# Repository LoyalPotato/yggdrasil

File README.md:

<div align="center">
  
</div>

</br>
</br>

# Welcome

[![CC BY-NC-SA 4.0][cc-by-nc-sa-shield]][cc-by-nc-sa]

This is the home of my first keyboard project that I dubbed `Yggdrasil`.

It's a 36% split keyboard that is tailored to be comfortable to my hand span. You can find the build guide [here](./docs/build.md).

You can view [here](https://www.youtube.com/watch?v=r2uFzhUAN9s) to see it in action.

Here's what it looks like (minus plates)

And with 3d printed plates (and custom cables also done by me hehe :) )

Full wrap around case, also 3d printed

## Contents

- [Welcome](#welcome)
  - [Contents](#contents)
  - [Design Article](#design-article)
  - [Plans](#plans)
  - [References](#references)
  - [License](#license)

## Design Article

If you're interested in knowing more about the design process that I went through and the final cost for me (in Portugal), I wrote a [post](https://loyalpotato.com/projects/yggdrasil) about it :)

## Plans

You can go to the projects tab to see what my current plans for the first version of this board are.

~~I do plan on making a low profile kailh choc variant, but only after I complete the cherry variant will I start working on a choc one.~~ I ended up using a footprint that has support for both :)

At some point I also would like to add to each version an alternative with a rotary encoder, and will create separate variants for that as well.

After I get more familiar with the process of pcb design and manufacturing I'd like to have a try at having a modular pcb, like the corne, where we can break the extra keys that you don't need.

---

## References

- [Ergogen](https://github.com/ergogen/ergogen) and the kind people from their [discord](https://discord.gg/nbKcAZB)
- [Ben Vallack's](https://github.com/benvallack/ergogen) flipper ergogen config and his youtube [video](https://www.youtube.com/watch?v=UKfeJrRIcxw)
- [Corne Kbd](https://github.com/foostan/crkbd)
- [ruiqimao's guide](https://github.com/ruiqimao/keyboard-pcb-guide)
- [tapioki's Architeuthis dux](https://github.com/tapioki/cephalopoda/tree/main/Architeuthis%20dux)
- [Lily58](https://github.com/kata0510/Lily58)
- [Keyboard Atelier's Discord](https://discord.gg/b7vwhHS)

## License

This work is licensed under a [Creative Commons Attribution-ShareAlike 4.0 International License][cc-by-nc-sa].

[![CC BY-NC-SA 4.0][cc-by-nc-sa-image]][cc-by-nc-sa]

[cc-by-nc-sa]: http://creativecommons.org/licenses/by-nc-sa/4.0/
[cc-by-nc-sa-image]: https://licensebuttons.net/l/by-nc-sa/4.0/88x31.png
[cc-by-nc-sa-shield]: https://img.shields.io/badge/License-CC%20BY--NC--SA%204.0-lightgrey.svg

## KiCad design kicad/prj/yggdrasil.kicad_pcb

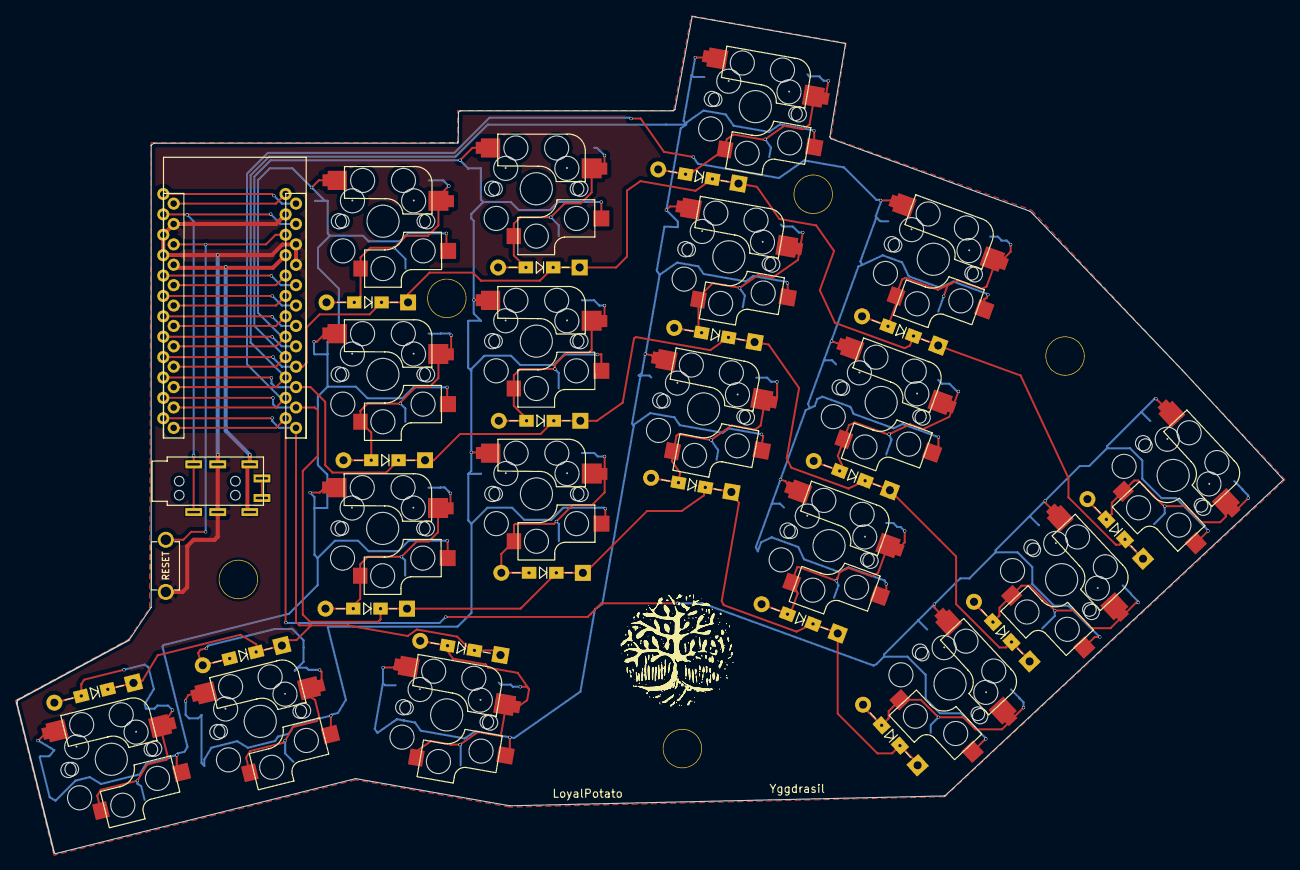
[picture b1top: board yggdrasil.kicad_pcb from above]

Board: 2 copper layers, 157.8 x 104.3 mm, 44 parts (0 on the bottom side), 31 nets.

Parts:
D1, D2, D3, D4, D5, D6, D7, D8, D9, D10, D11, D12, D13, D14, D15, D16, D17, D18: D; Diode_TH_SOD123
J2: 4PIN; MJ-4PP-9
RSW1: SW_RST; TACT_SWITCH_TVBP06
SW1, SW2, SW3, SW4, SW5, SW6, SW7, SW8, SW9, SW10, SW11, SW12, SW13, SW14, SW15, SW16, SW17, SW18: SW_PUSH; Cherry_MX_Choc_Hotswap_MX_Spacing
TH3, TH4, TH5, TH6, TH7: HOLE; HOLE_M2_TH
U1: ProMicro; ProMicro_USB_C

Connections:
DATA: J2.3, U1.2 (RX(PD2))
GND: J2.2, RSW1.1, U1.3 (GND), U1.4 (GND), U1.23 (GND)
unnamed: D1.2 (A), SW1.2
unnamed: D2.2 (A), SW2.2
unnamed: D3.2 (A), SW3.2
unnamed: D4.2 (A), SW4.2
unnamed: D5.2 (A), SW5.2
unnamed: D6.2 (A), SW6.2
unnamed: D7.2 (A), SW7.2
unnamed: D8.2 (A), SW8.2
unnamed: D9.2 (A), SW9.2
unnamed: D10.2 (A), SW10.2
unnamed: D11.2 (A), SW11.2
unnamed: D12.2 (A), SW12.2
unnamed: D13.2 (A), SW13.2
unnamed: D14.2 (A), SW14.2
unnamed: D15.2 (A), SW15.2
unnamed: D16.2 (A), SW16.2
unnamed: D17.2 (A), SW17.2
unnamed: D18.2 (A), SW18.2
RESET: RSW1.2, U1.22 (RST)
VCC: J2.1, U1.21 (VCC)
col0: SW1.1, SW6.1, SW11.1, SW16.1, U1.17 (A0(PF7))
col1: SW2.1, SW7.1, SW12.1, SW17.1, U1.16 (D15(PB1))
col2: SW3.1, SW8.1, SW13.1, SW18.1, U1.15 (D14(PB3))
col3: SW4.1, SW9.1, SW14.1, U1.14 (D16(PB2))
col4: SW5.1, SW10.1, SW15.1, U1.13 (D10(PB6))
row0: D1.1 (K), D2.1 (K), D3.1 (K), D4.1 (K), D5.1 (K), U1.9 (D6(PD7))
row1: D6.1 (K), D7.1 (K), D8.1 (K), D9.1 (K), D10.1 (K), U1.10 (D7(PE6))
row2: D11.1 (K), D12.1 (K), D13.1 (K), D14.1 (K), D15.1 (K), U1.11 (D8(PB4))
row3: D16.1 (K), D17.1 (K), D18.1 (K), U1.12 (D9(PB5))

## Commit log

2022-02-21 Capitalize
2022-02-21 Add build doc for cherry variant
2022-02-21 Doc file for choc switches build guide
2022-02-21 Renaming and re-structuring
2022-02-21 Add logos
2022-02-21 Test logos in readme
2022-02-21 Remove no bg logo and reduce size
2022-02-21 Add logo with name
2022-02-21 Use named version for logo
2022-02-21 Update readme with refs, content and plans
2022-02-21 Add ergogen file configurations and notes
2022-02-21 Update plans
2022-02-21 Remove one spacing
2022-02-21 Add outlines for keycaps and edge from ergogen config
2022-02-21 Re organize ergogen folder
2022-02-21 Add description to ergogen config sections
2022-02-23 Update logo with text
2022-02-23 Remove variants and replace with single version that will support both types
2022-02-23 Add kicad backup folder to gitignore
2022-02-24 Outlines v1
2022-02-28 Lily58 footprints
2022-02-28 kbd footprints
2022-02-28 kbd symbol lib
2022-02-28 Lily58 symbol lib
2022-02-28 Kicad project
2022-03-01 Add custom footprints Hotswap switch with cherry keycap spacing Different measurements for promicro with usb-c
2022-03-01 Updated spacing Re-do edge cuts Some routing Diode placement Screwhole placement
2022-03-02 Logo with and without text in png format for kicad
2022-03-02 Change switch keycap spacing Add routing Add ground plane Add logo & text
2022-03-02 Footprint for logo
2022-03-02 Files missed in previous commits
2022-03-03 Update readme plans and refs
2022-03-03 Clean up/straighten routings
2022-03-03 Add image with board outline and switch placement
2022-03-03 Kicad prj update
2022-03-03 Change license
2022-03-03 Update with license
2022-03-03 Re update license section
2022-03-03 Re-update license
2022-03-03 Update license title
2022-03-03 Update license link ref
2022-03-03 Add gerber
2022-03-03 Prj files
2022-03-05 Add plates for first revision Still need to confirm if everything works out
2022-03-05 Deleted outlines folder as I haven't used it so far
2022-03-05 Revision 1.0.1 Fixed wrong rotation, some spacing and clearences
2022-03-05 Rev 1 prj
2022-03-05 Some revision notes
2022-03-05 Remove backup folders
2022-03-05 Add small description of the keyboard
2022-03-05 Update build with part list that I will be using
2022-03-05 Change TRRS jack ( ordered smd ;w;)
2022-04-04 Fix USB-C ProMicro link
2022-04-30 Build guide almost finished
2022-04-30 Add semi final image to cover
2022-04-30 Add build guide ref
2022-09-13 Add svg plates
2022-09-22 Bot plate, still needs some improvement
2022-09-30 Add img with more complete build
2022-10-05 Add video
2022-10-15 Add plates
2022-10-15 New media & imgs
2022-12-29 Add link to design article
